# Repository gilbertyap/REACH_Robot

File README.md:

Imported from [Gilbert Yap's GitHub](https://github.com/gilbertyap/REACH_Robot)

# REACH_Robot
[Northeastern University ReGame-VR Lab](http://www.northeastern.edu/regamevrlab/) [REACH Robot](https://www.northeastern.edu/rise/presentations/motion-capture-based-robotic-interfaces-enhance-engagement-adherence-pediatric-rehabilitation/) software

## Software requirements
- Leap Motion Controller SDK (currently using ~~version 2.3.1, *NOT* the~~ Orion SDK (versions 3 and up) ~~which made changes to specific function calls~~ (02/21/2018 code working with Orion version 3))
- Python 2.7 (version 3 is incompatible with current code)
- PyCharm Community Edition for running Leap code in a terminal window
- Arduino IDE
- [Feather M0 RFM95 drivers](https://learn.adafruit.com/adafruit-feather-m0-radio-with-RFM95-packet-radio/setup)

## Folder breakdown

###### Hardware Requirements
- Leap Motion controller
- Adafruit Feather M0 RFM95 x 3
- [Computer that meets the Leap Motion Controller minimum requirements](https://support.leapmotion.com/hc/en-us/articles/223783668-What-are-the-system-requirements-)
- At least two (2) dedicated USB ports (splitters will not work) for the Leap Motion controller and one (1) Feather M0 RFM95

###### ReachLeap and ReachLeap_Rotate
These folders contain the Python code for recognizing movement with the Leap Motion controller. The ```_rotate``` suffix refers to using rotational movement system, whereas no suffix refers to XYZ coordinate movement. These folder rely on a text file with the limitations of movement, currently titled ```test_limits.txt```. Hand positions relative to these limits are calculated and converted to motor positions for the robot arm, then sent over serial to the Feather M0 RFM95 connected to the computer via USB.

###### LeapCalibrate and LeapCalibrate_Rotate
These folders are used for calibrating the Leap Motion controller REACH software (ReachLeap and ReachLeap_Rotate) to the range of movement of the user.

###### LeapAssests
This folder contains necessary files for using Leap with Python

**_NOTE FOR THE ABOVE FOLDERS: Depending on the computer system, it may require changing the Leap.dll and LeapPython.pyd. Check the LeapAssests folder for the 32-bit (x86) and 64-bit (x64) files_**

###### RobotArm_Feather/ServoArm
This folder contains the code for the Feather M0 RFM95 that is used to control the robot arm and the wheeled-base. The code receives the motor position data that was wireless transmitted from the computer and sets the motors on the arm accordingly. This code is also responsible for controlling the wheels on the base, which is wireless transmitted from a joystick using another Feather M0 RFM95.

###### RobotArm_Photon/ServoArm
Outdated code for use with the Particle Photon. With the switch to RF-based Feather M0 RFM95, this code is obsolete.

###### TX_Computer_Transceiver/computer_tx_leap
This folder contains the code for the Feather M0 RFM95 that will be connected to the computer using the Leap Motion controller. The Feather M0 RFM95 can be programmed with [this guide](https://learn.adafruit.com/adafruit-feather-m0-radio-with-RFM95-packet-radio/using-with-arduino-ide). The serial data containing the motor positions from the ReachLeap/ReachLeap_Rotate software is then wireless transmitted to the arm/base with a matching microcontroller.

###### Base_Joystick
This folder will contain the code for the Feather M0 RFM95 that reads joystick data and sends it wirelessly.

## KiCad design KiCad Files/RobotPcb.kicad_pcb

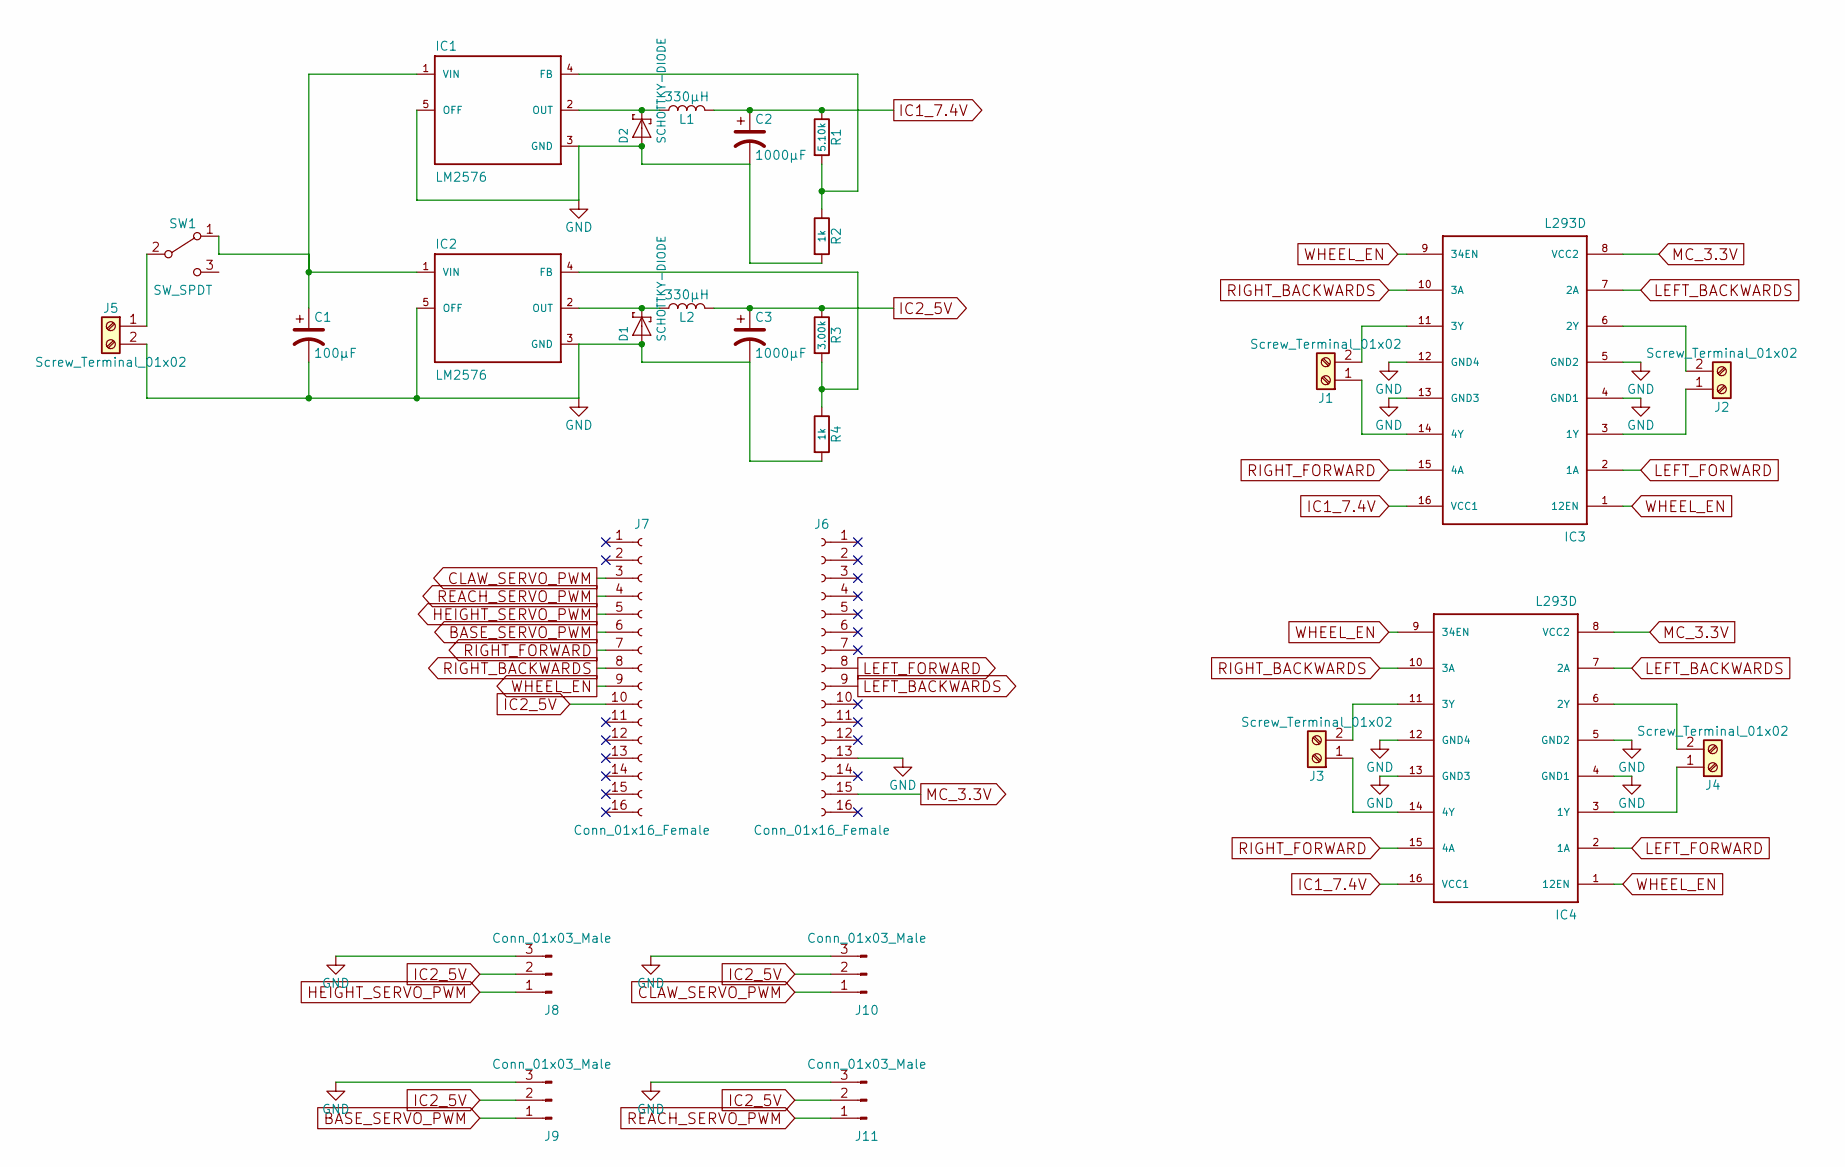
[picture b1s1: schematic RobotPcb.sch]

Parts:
C1: 100μF; CP_Radial_D6.3mm_P2.50mm
C2, C3: 1000μF; CP_Radial_D6.3mm_P2.50mm
D1, D2: SCHOTTKY-DIODE; D_DO-201AD_P12.70mm_Horizontal
IC1, IC2: LM2576; TO-220-5
IC3, IC4: L293D; DIP-16_W7.62mm_Socket
J1, J2, J3, J4, J5: Screw_Terminal_01x02; TerminalBlock_Altech_AK300-2_P5.00mm
J6, J7: Conn_01x16_Female; Socket_Strip_Straight_1x16_Pitch2.54mm
J8, J9, J10, J11: Conn_01x03_Male; Pin_Header_Straight_1x03_Pitch2.54mm
L1, L2: 330μH; L_Toroid_Vertical_L19.1mm_W8.1mm_P7.10mm_Bourns_5700
R1: 5.10k; R_Axial_DIN0207_L6.3mm_D2.5mm_P7.62mm_Horizontal
R2, R4: 1k; R_Axial_DIN0207_L6.3mm_D2.5mm_P7.62mm_Horizontal
R3: 3.00k; R_Axial_DIN0207_L6.3mm_D2.5mm_P7.62mm_Horizontal
SW1: SW_SPDT; L102021ML04Q_SPDT

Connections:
BASE_SERVO_PWM: J7.6, J9.1
CLAW_SERVO_PWM: J7.3, J10.1
GND: C1.2, C2.2, C3.2, D1.2, D2.2, IC1.3 (GND), IC1.5 (OFF), IC2.3 (GND), IC2.5 (OFF), IC3.4 (GND1), IC3.5 (GND2), IC3.12 (GND4), IC3.13 (GND3), IC4.4 (GND1), IC4.5 (GND2), IC4.12 (GND4), IC4.13 (GND3), J5.2, J6.13, J8.3, J9.3, J10.3, J11.3, R2.2, R4.2
HEIGHT_SERVO_PWM: J7.5, J8.1
IC1_7.4V: C2.1, IC3.16 (VCC1), IC4.16 (VCC1), L1.2, R1.1
IC2_5V: C3.1, J7.10, J8.2, J9.2, J10.2, J11.2, L2.2, R3.1
LEFT_BACKWARDS: IC3.7 (2A), IC4.7 (2A), J6.9
LEFT_FORWARD: IC3.2 (1A), IC4.2 (1A), J6.8
MC_3.3V: IC3.8 (VCC2), IC4.8 (VCC2), J6.15
unnamed: C1.1, IC1.1 (VIN), IC2.1 (VIN), SW1.1 (A)
unnamed: D1.1, IC2.2 (OUT), L2.1
unnamed: D2.1, IC1.2 (OUT), L1.1
unnamed: IC1.4 (FB), R1.2, R2.1
unnamed: IC2.4 (FB), R3.2, R4.1
unnamed: IC3.3 (1Y), J2.1
unnamed: IC3.6 (2Y), J2.2
unnamed: IC3.11 (3Y), J1.2
unnamed: IC3.14 (4Y), J1.1
unnamed: IC4.3 (1Y), J4.1
unnamed: IC4.6 (2Y), J4.2
unnamed: IC4.11 (3Y), J3.2
unnamed: IC4.14 (4Y), J3.1
unnamed: J5.1, SW1.2 (B)
REACH_SERVO_PWM: J7.4, J11.1
RIGHT_BACKWARDS: IC3.10 (3A), IC4.10 (3A), J7.8
RIGHT_FORWARD: IC3.15 (4A), IC4.15 (4A), J7.7
WHEEL_EN: IC3.1 (12EN), IC3.9 (34EN), IC4.1 (12EN), IC4.9 (34EN), J7.9

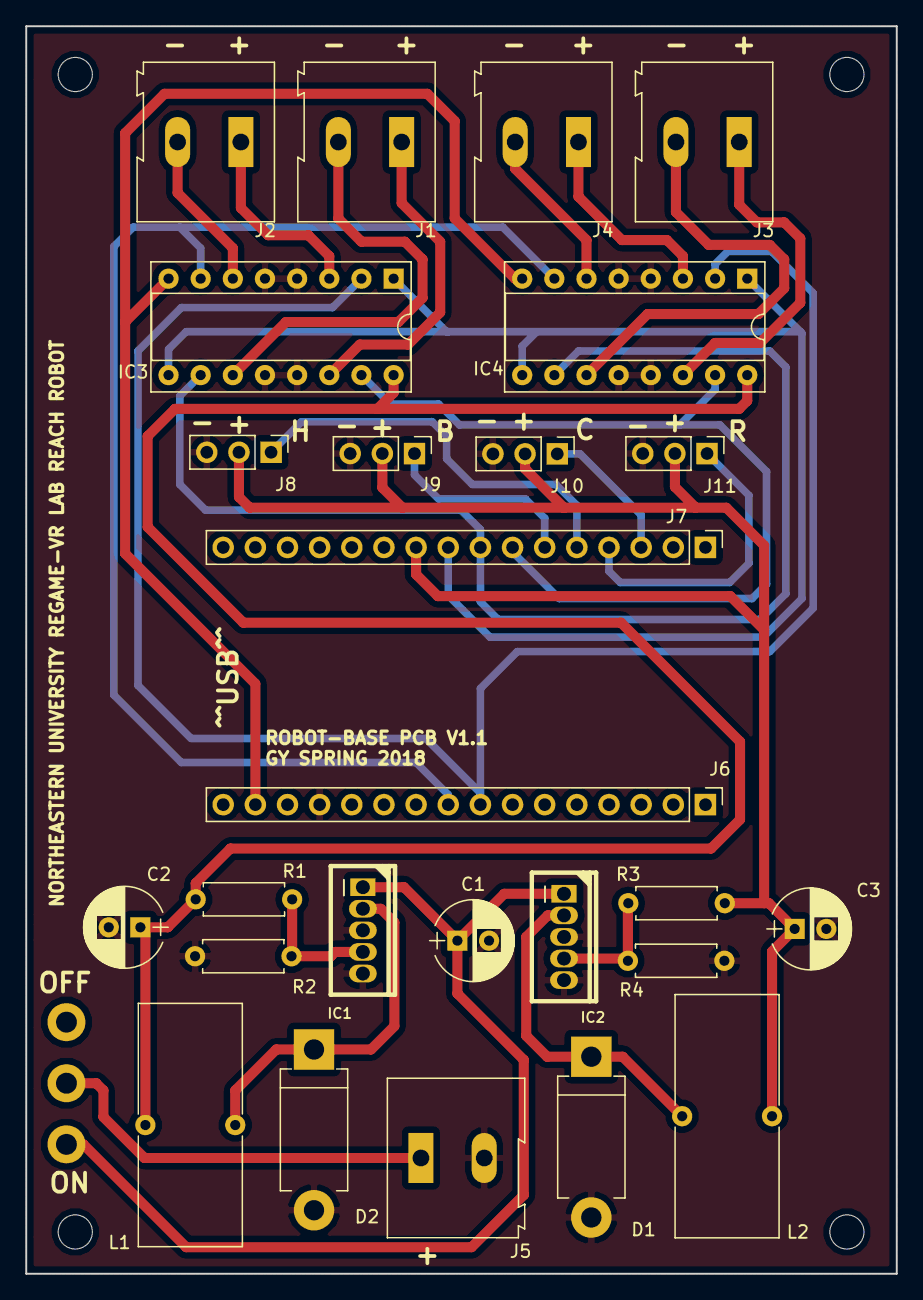
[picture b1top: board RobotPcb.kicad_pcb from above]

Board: 2 copper layers, 68.8 x 98.6 mm, 27 parts (0 on the bottom side), 27 nets.

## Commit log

2017-02-22 End of Fall 2016 code
2017-04-15 Limit to right hand
    Also added pause by close fist
2018-01-19 Wireless code for arm and computer-side added
2018-01-19 Made note for outdated Photon code
2018-01-19 Updated readme, added 32/64-bit assests
2018-01-19 Fixed readme
2018-01-19 Changes to serial message, optimizations
2018-01-23 Fixed tranceiver model number
2018-02-04 Fixes to frame gathering and hand position data
2018-02-08 Joystick transmission, timers added
2018-02-21 main not working, check new branch for fix
2018-02-21 Fixed averaging issue, more comments
2018-02-22 Base motor control, scheduler, joystick finishes
2018-03-30 Added preliminary schematic files (Immanuel init)
2018-04-11 PCB Files added
2018-04-27 Fixed PCBs
    PCB v1.1
    Added schematic PDF, updated pinout for PCB
2018-04-27 Added KiCad folder description
2018-04-30 starting branch
